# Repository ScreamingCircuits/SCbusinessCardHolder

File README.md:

# SCbusinessCardHolder
Screaming Circuits business card holder, V2.1

The Screaming Circuits business card holder is a multi-function device intended for your amusement and as a demonstration of our workmanship.

After soldering in the pin headers, attaching the rubber feet, and inserting the batteries, it’s ready to go. Place it on your desk and put about ten business cards in. When someone takes a card (or if you pound on your keyboard hard enough) some of the LEDs will flash.

If you tip it up, so that the LEDs run along the bottom, it will act as a spirit level, and as a short ruler. It’s not angle calibrated. Doing so is up to you. 

The microcontroller fitted is of the Microchip PIC18F46K22 family. The initial version was produced with a PIC18F43K22 – the same, but with less FLASH and SRAM. The accelerometer is a Freescale MMA8452Q. The schematic and layout were created with EagleCAD. The code was written and compiled with Microchip XC8 in Mplab-X.

One of the pin headers is connected to the I2C and SPI bus pins on the MCU. The other is connected to the Microchip ICSP (in circuit serial programming) pins on the MCU. Button Usr 1 is connected to I/O pin RB4, and Usr 2 is connected to RB5.

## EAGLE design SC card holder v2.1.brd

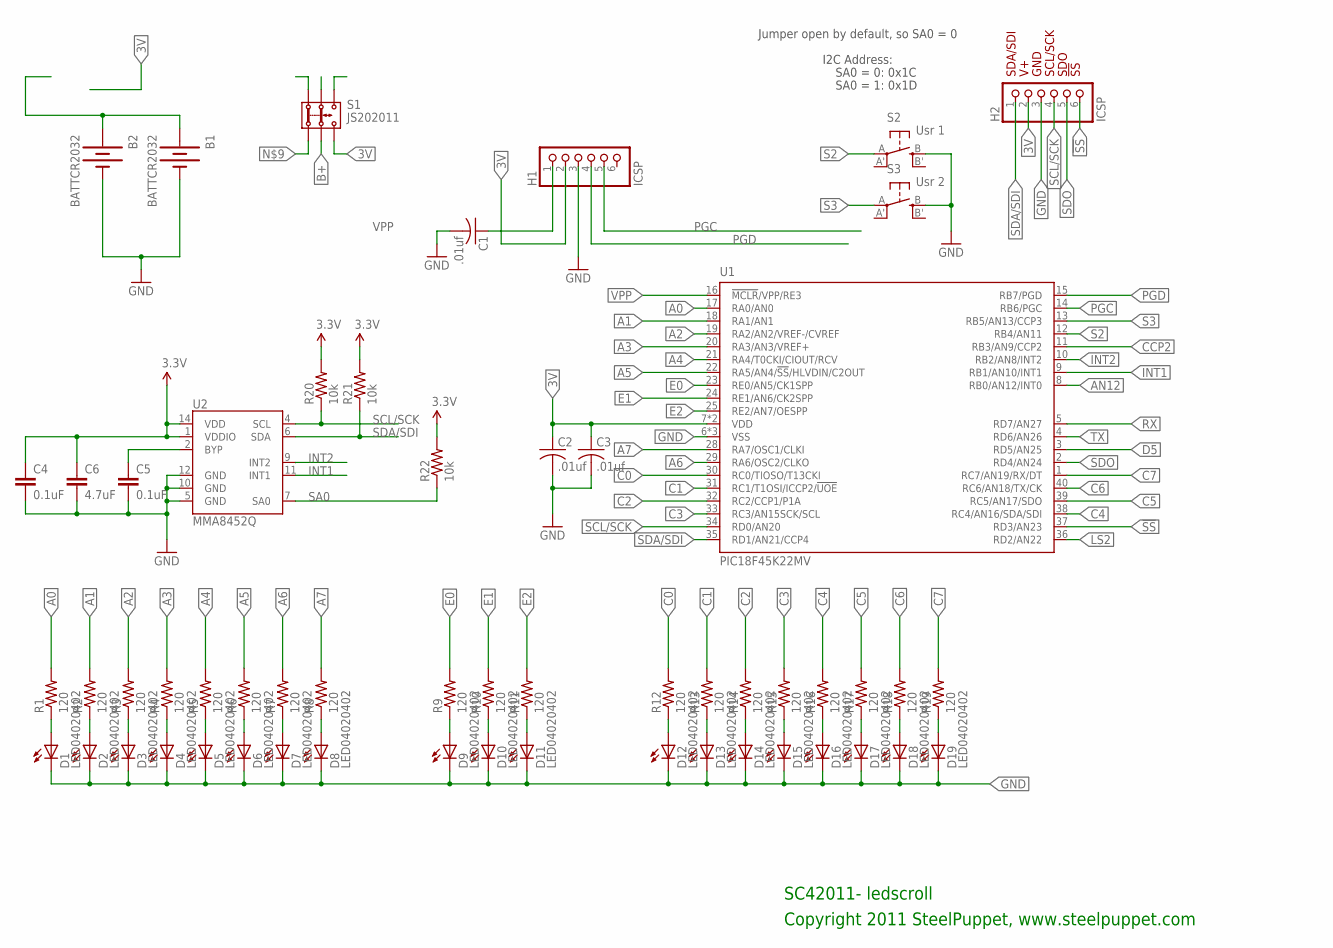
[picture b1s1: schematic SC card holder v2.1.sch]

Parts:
B1, B2: BATTCR2032; BATT_2032_SMT
C1, C2, C3: .01uf; C0402K
C4, C5: 0.1uF; 0402-CAP
C6: 4.7uF; 0402-CAP
D1, D2, D3, D4, D5, D6, D7, D8, D9, D10, D11, D12, D13, D14, D15, D16, D17, D18, D19: LED04020402; LED0402
H1, H2: ICSP; 1X06-S
R1, R2, R3, R4, R5, R6, R7, R8, R9, R10, R11, R12, R13, R14, R15, R16, R17, R18, R19: 120; R0402
R20, R21, R22: 10k; 0402-RES
S1: JS202011; JS202011SMT
S2: Usr 1; EVQ-Q2
S3: Usr 2; EVQ-Q2
U1: PIC18F45K22MV; QFN40-5X5
U2: MMA8452Q; QFN-16_0.5MM

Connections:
3V: C2.1, C3.1, C4.1, C6.1, H1.2, H2.2, R20.2, R21.2, R22.2, S1.3 (3.2), S1.4 (3.1), U1.7 (VDD), U1.26 (VDD), U2.1 (VDDIO), U2.14 (VDD)
!SS: H2.6, U1.37 (RD3/AN23)
A0: R1.2, U1.17 (RA0/AN0)
A1: R2.2, U1.18 (RA1/AN1)
A2: R3.2, U1.19 (RA2/AN2/VREF-/CVREF)
A3: R4.2, U1.20 (RA3/AN3/VREF+)
A4: R5.2, U1.21 (RA4/T0CKI/CIOUT/RCV)
A5: R6.2, U1.22 (RA5/AN4/!SS!/HLVDIN/C2OUT)
A6: R7.2, U1.29 (RA6/OSC2/CLKO)
A7: R8.2, U1.28 (RA7/OSC1/CLKI)
AN12: U1.8 (RB0/AN12/INT0)
B+: B1.1 (+), B1.3 (+), B2.1 (+), B2.3 (+), S1.2 (2.2), S1.5 (2.1)
BYP: C5.1, U2.2 (BYP)
C0: R12.2, U1.30 (RC0/TIOSO/T13CKI)
C1: R13.2, U1.31 (RC1/T1OSI/ICCP2/!UOE)
C2: R14.2, U1.32 (RC2/CCP1/P1A)
C3: R15.2, U1.33 (RC3/AN15SCK/SCL)
C4: R16.2, U1.38 (RC4/AN16/SDA/SDI)
C5: R17.2, U1.39 (RC5/AN17/SDO)
C6: R18.2, U1.40 (RC6/AN18/TX/CK)
C7: R19.2, U1.1 (RC7/AN19/RX/DT)
CCP2: U1.11 (RB3/AN9/CCP2)
D5: U1.3 (RD5/AN25)
E0: R9.2, U1.23 (RE0/AN5/CK1SPP)
E1: R10.2, U1.24 (RE1/AN6/CK2SPP)
E2: R11.2, U1.25 (RE2/AN7/OESPP)
GND: B1.2 (-), B2.2 (-), C1.2, C2.2, C3.2, C4.2, C5.2, C6.2, D1.C, D2.C, D3.C, D4.C, D5.C, D6.C, D7.C, D8.C, D9.C, D10.C, D11.C, D12.C, D13.C, D14.C, D15.C, D16.C, D17.C, D18.C, D19.C, H1.3, H2.3, S2.B (S), S3.B (S), U1.6 (VSS), U1.27 (VSS), U1.41 (VSS), U2.5 (GND), U2.10 (GND), U2.12 (GND)
INT1: U1.9 (RB1/AN10/INT1), U2.11 (INT1)
INT2: U1.10 (RB2/AN8/INT2), U2.9 (INT2)
LS2: U1.36 (RD2/AN22)
unnamed: D1.A, R1.1
unnamed: D2.A, R2.1
unnamed: D3.A, R3.1
unnamed: D4.A, R4.1
unnamed: D9.A, R9.1
unnamed: D10.A, R10.1
unnamed: D11.A, R11.1
unnamed: D13.A, R13.1
unnamed: D14.A, R14.1
unnamed: D15.A, R15.1
unnamed: D12.A, R12.1
unnamed: D6.A, R6.1
unnamed: D7.A, R7.1
unnamed: D16.A, R16.1
unnamed: D17.A, R17.1
unnamed: D8.A, R8.1
unnamed: D5.A, R5.1
unnamed: D18.A, R18.1
unnamed: D19.A, R19.1
PGC: H1.5, U1.14 (RB6/PGC)
PGD: H1.4, U1.15 (RB7/PGD)
RX: U1.5 (RD7/AN27)
S2: S2.A, U1.12 (RB4/AN11)
S3: S3.A, U1.13 (RB5/AN13/CCP3)
SA0: R22.1, U2.7 (SA0)
SCL/SCK: H2.4, R20.1, U1.34 (RD0/AN20), U2.4 (SCL)
SDA/SDI: H2.1, R21.1, U1.35 (RD1/AN21/CCP4), U2.6 (SDA)
SDO: H2.5, U1.2 (RD4/AN24)
TX: U1.4 (RD6/AN26)
VPP: C1.1, H1.1, U1.16 (!MCLR!/VPP/RE3)

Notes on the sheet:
SC42011- ledscroll
Copyright 2011 SteelPuppet, www.steelpuppet.com
SDA/SDI
GND
SCL/SCK
SDO
!SS
I2C Address:
SA0 = 0: 0x1C
SA0 = 1: 0x1D
Jumper open by default, so SA0 = 0

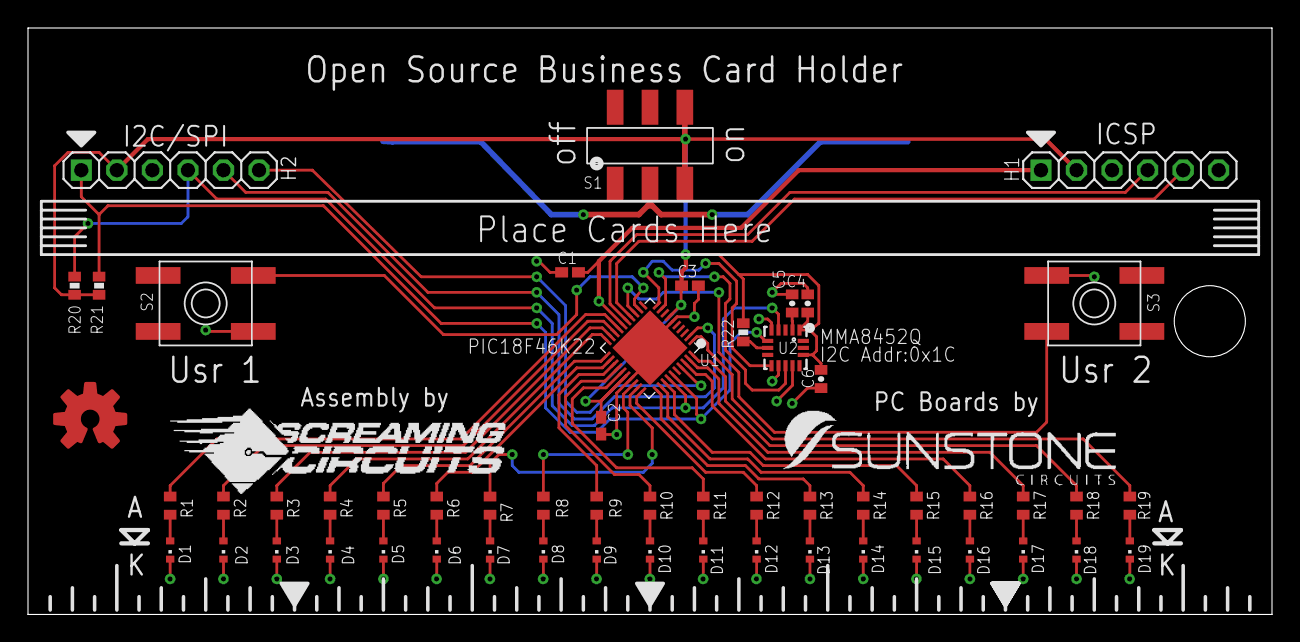
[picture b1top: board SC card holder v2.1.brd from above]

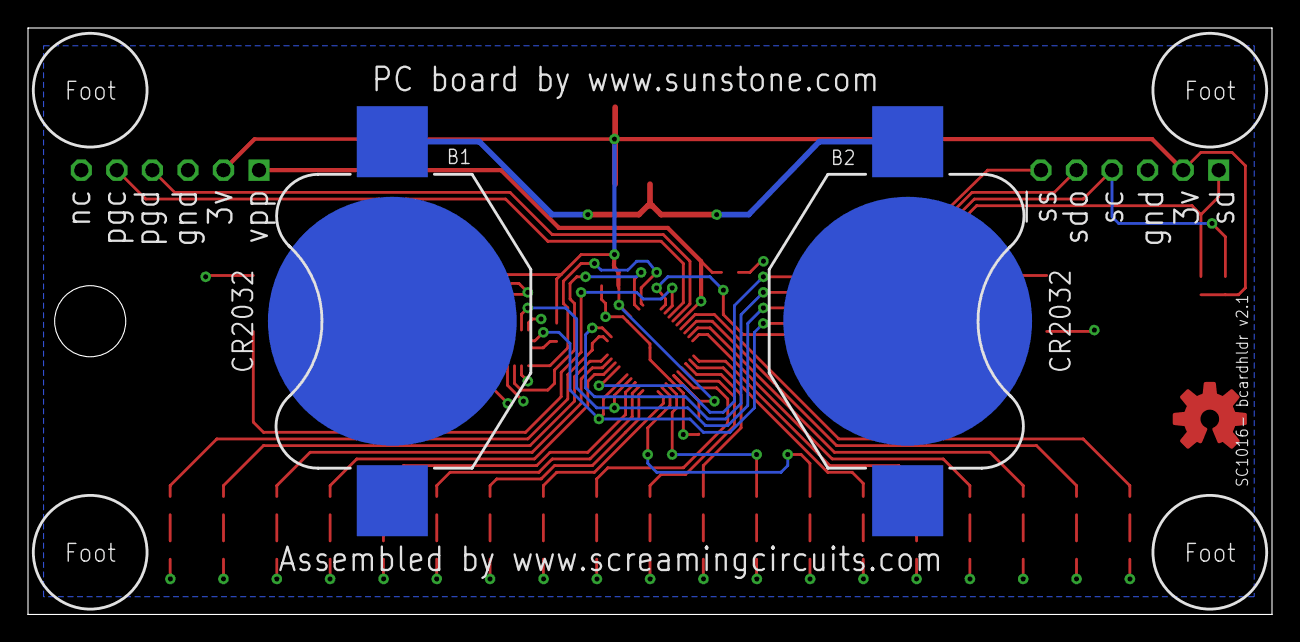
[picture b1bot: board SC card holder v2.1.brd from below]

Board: 2 copper layers, 88.9 x 41.9 mm, 59 parts (2 on the bottom side), 54 nets.

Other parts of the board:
U$1: SUNSTONE-LOGO
U$2: OSHWLOGO_TOP_0.2
U$3: SC-LOGO
